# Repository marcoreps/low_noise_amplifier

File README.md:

# low_noise_amplifier

not finished!

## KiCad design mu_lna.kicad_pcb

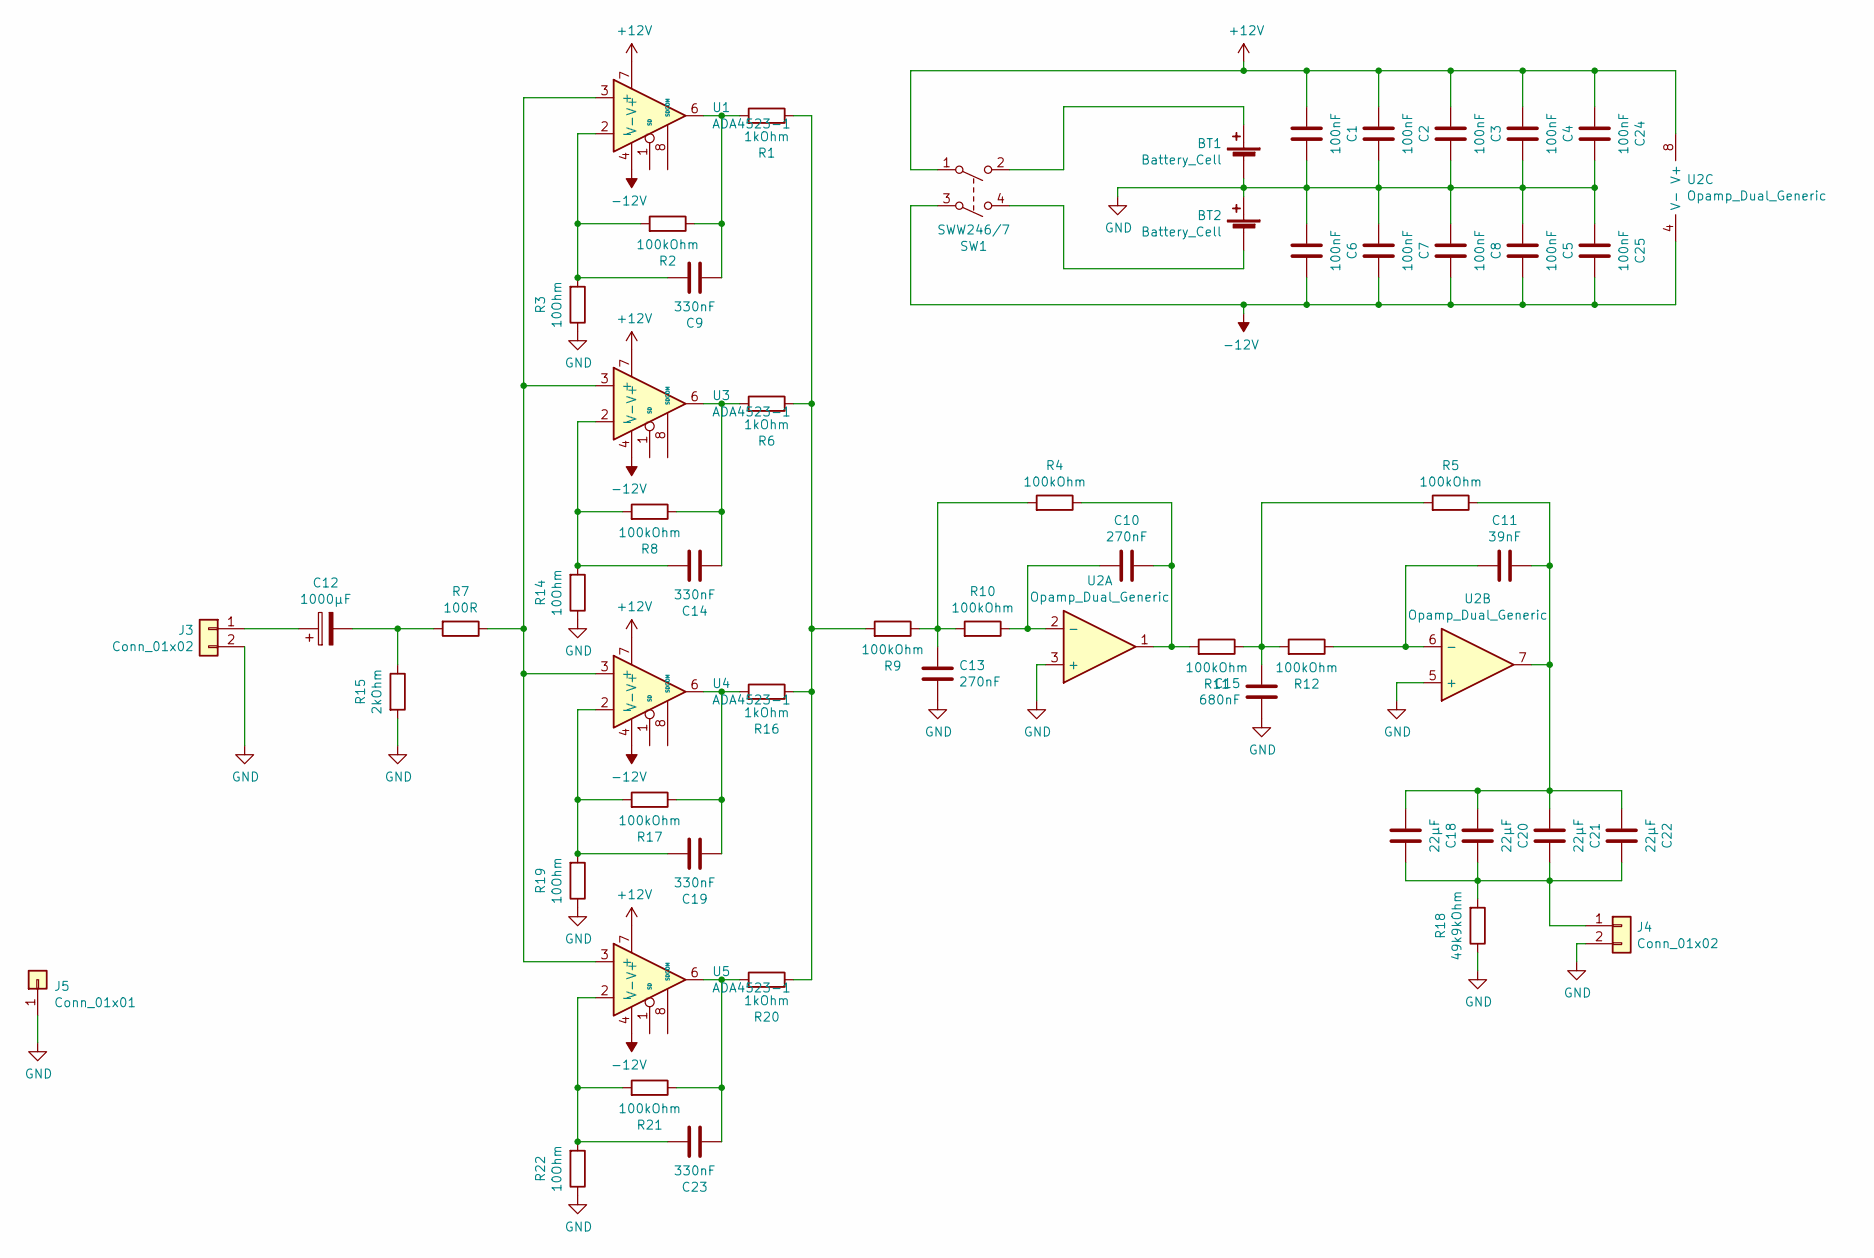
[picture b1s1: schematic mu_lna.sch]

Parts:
BT1, BT2: Battery_Cell; 9V_Keystone_593_594
C1, C2, C3, C4, C5, C6, C7, C8, C24, C25: 100nF; C_0603_1608Metric
C9, C14, C19, C23: 330nF; C_0603_1608Metric
C10, C13: 270nF; C_0603_1608Metric
C11: 39nF; C_0603_1608Metric
C12: 1000µF; CP_Radial_D16.0mm_P7.50mm
C15: 680nF; C_0603_1608Metric
C18, C20, C21, C22: 22µF; C_1210_3225Metric
J3, J4: Conn_01x02; BNC_Amphenol_B6252HB-NPP3G-50_Horizontal
J5: Conn_01x01; Laird_Technologies_BMI-S-209-F_29.36x18.50mm
R1, R6, R16, R20: 1kOhm; R_0603_1608Metric
R2, R4, R5, R8, R9, R10, R11, R12, R17, R21: 100kOhm; R_0603_1608Metric
R3, R14, R19, R22: 10Ohm; R_0603_1608Metric
R7: 100R; R_0805_2012Metric
R15: 2kOhm; R_0805_2012Metric
R18: 49k9kOhm; R_0603_1608Metric
SW1: SWW246/7; RS_DPDT
U1, U3, U4, U5: ADA4523-1; SOIC-8_3.9x4.9mm_P1.27mm
U2: Opamp_Dual_Generic; MSOP-8_3x3mm_P0.65mm

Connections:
+12V: C1.1, C2.1, C3.1, C4.1, C24.1, SW1.1, U1.7 (V+), U2.8 (V+), U3.7 (V+), U4.7 (V+), U5.7 (V+)
-12V: C5.2, C6.2, C7.2, C8.2, C25.2, SW1.3, U1.4 (V-), U2.4 (V-), U3.4 (V-), U4.4 (V-), U5.4 (V-)
GND: BT1.2 (-), BT2.1 (+), C1.2, C2.2, C3.2, C4.2, C5.1, C6.1, C7.1, C8.1, C13.1, C15.1, C24.2, C25.1, J3.2, J4.2, J5.1, R3.1, R14.1, R15.2, R18.1, R19.1, R22.1, SW1.7, SW1.8, U2.3 (+), U2.5 (+)
unnamed: BT1.1 (+), SW1.2
unnamed: BT2.2 (-), SW1.4
unnamed: C9.1, R1.2, R2.1, U1.6
unnamed: C9.2, R2.2, R3.2, U1.2 (-)
unnamed: C10.1, R10.1, U2.2 (-)
unnamed: C10.2, R4.1, R11.2, U2.1
unnamed: C11.1, R12.1, U2.6 (-)
unnamed: C11.2, C18.1, C20.1, C21.1, C22.1, R5.1, U2.7
unnamed: C12.1, J3.1
unnamed: C12.2, R7.2, R15.1
unnamed: C13.2, R4.2, R9.1, R10.2
unnamed: C14.1, R6.2, R8.1, U3.6
unnamed: C14.2, R8.2, R14.2, U3.2 (-)
unnamed: C15.2, R5.2, R11.1, R12.2
unnamed: C18.2, C20.2, C21.2, C22.2, J4.1, R18.2
unnamed: C19.1, R16.2, R17.1, U4.6
unnamed: C19.2, R17.2, R19.2, U4.2 (-)
unnamed: C23.1, R20.2, R21.1, U5.6
unnamed: C23.2, R21.2, R22.2, U5.2 (-)
unnamed: R1.1, R6.1, R9.2, R16.1, R20.1
unnamed: R7.1, U1.3 (+), U3.3 (+), U4.3 (+), U5.3 (+)

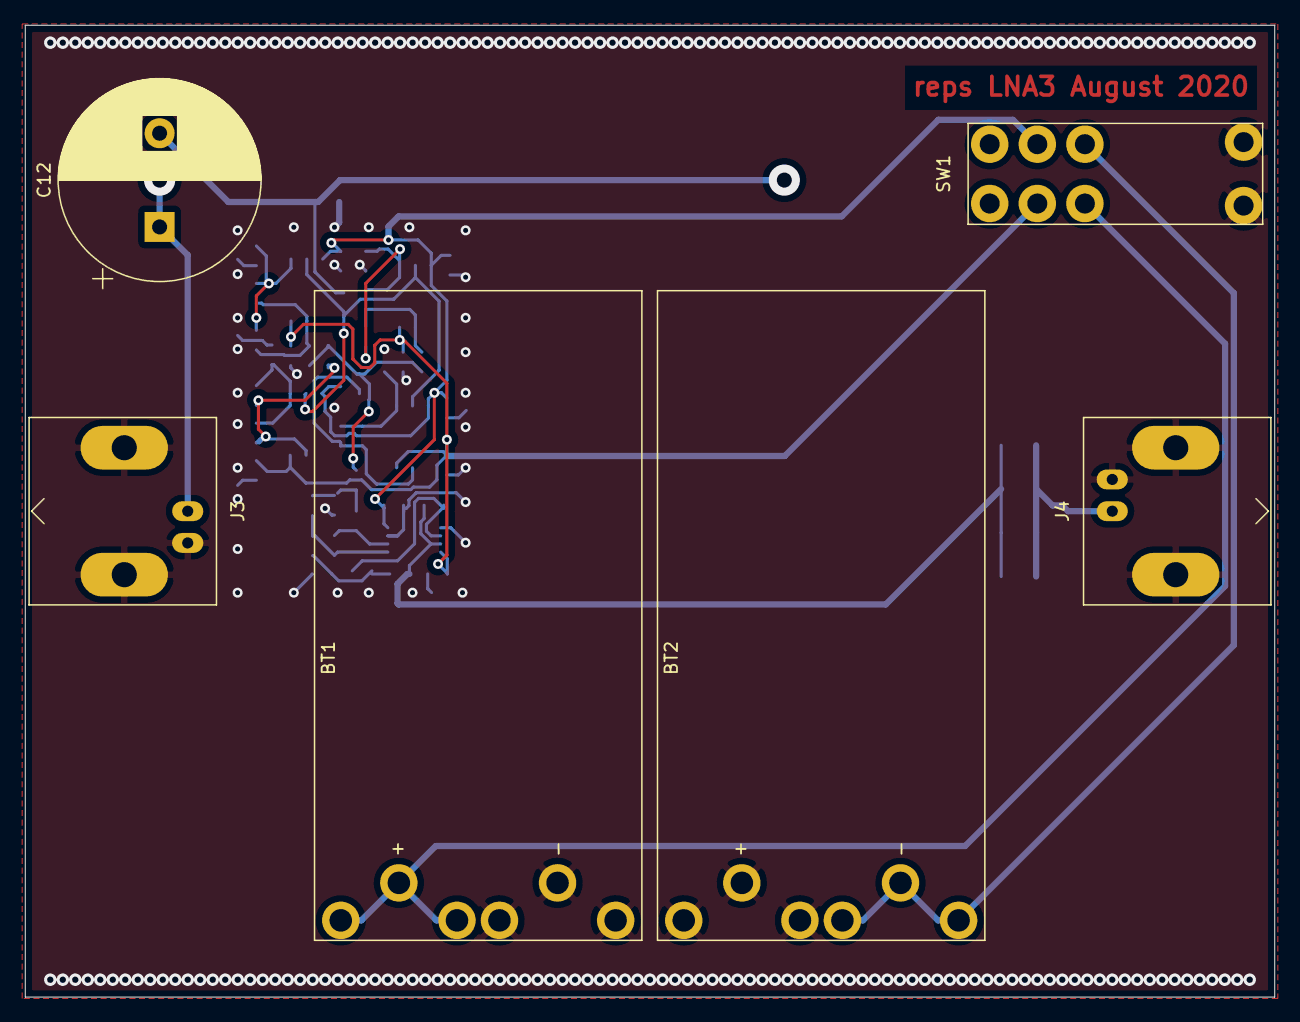
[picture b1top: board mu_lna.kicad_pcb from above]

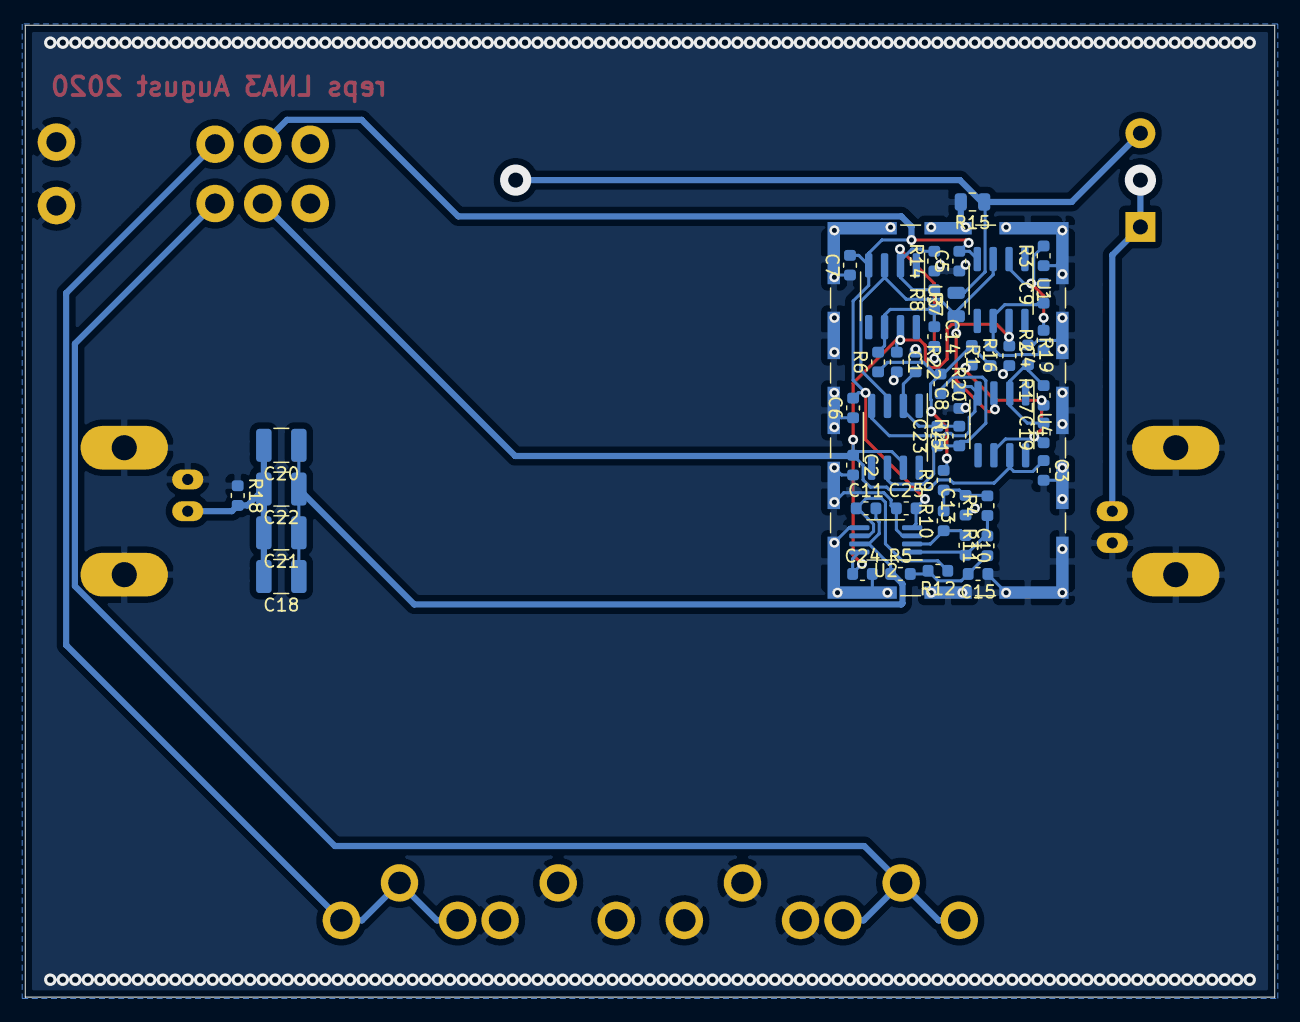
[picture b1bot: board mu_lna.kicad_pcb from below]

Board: 2 copper layers, 100.0 x 77.8 mm, 55 parts (49 on the bottom side), 24 nets.

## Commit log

2020-08-21 new layout for Bopla 84080100
2020-08-21 Added front and rear panels
2020-08-28 man, this is a pretty tight fit ...
